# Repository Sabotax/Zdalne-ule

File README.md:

# Zdalne-ule
Projekt przejściowy oraz praca inżynierska oraz projekt kontynuowany prywatnie.
Polega na zbieraniu danych z uli pszczeli w celu ich zdalnego wykorzystania w optymalizacji pracy pszczelarza.  

Używane technologie: 
	- C++ od strony mikontrolerów,

 \
	- Javascript/PHP od strony serwera
 \
	- Kotlin od strony aplikacji mobilnej

Prezentacja  
https://prezi.com/view/HmCi9ISC9FMyPvuT7w0S/

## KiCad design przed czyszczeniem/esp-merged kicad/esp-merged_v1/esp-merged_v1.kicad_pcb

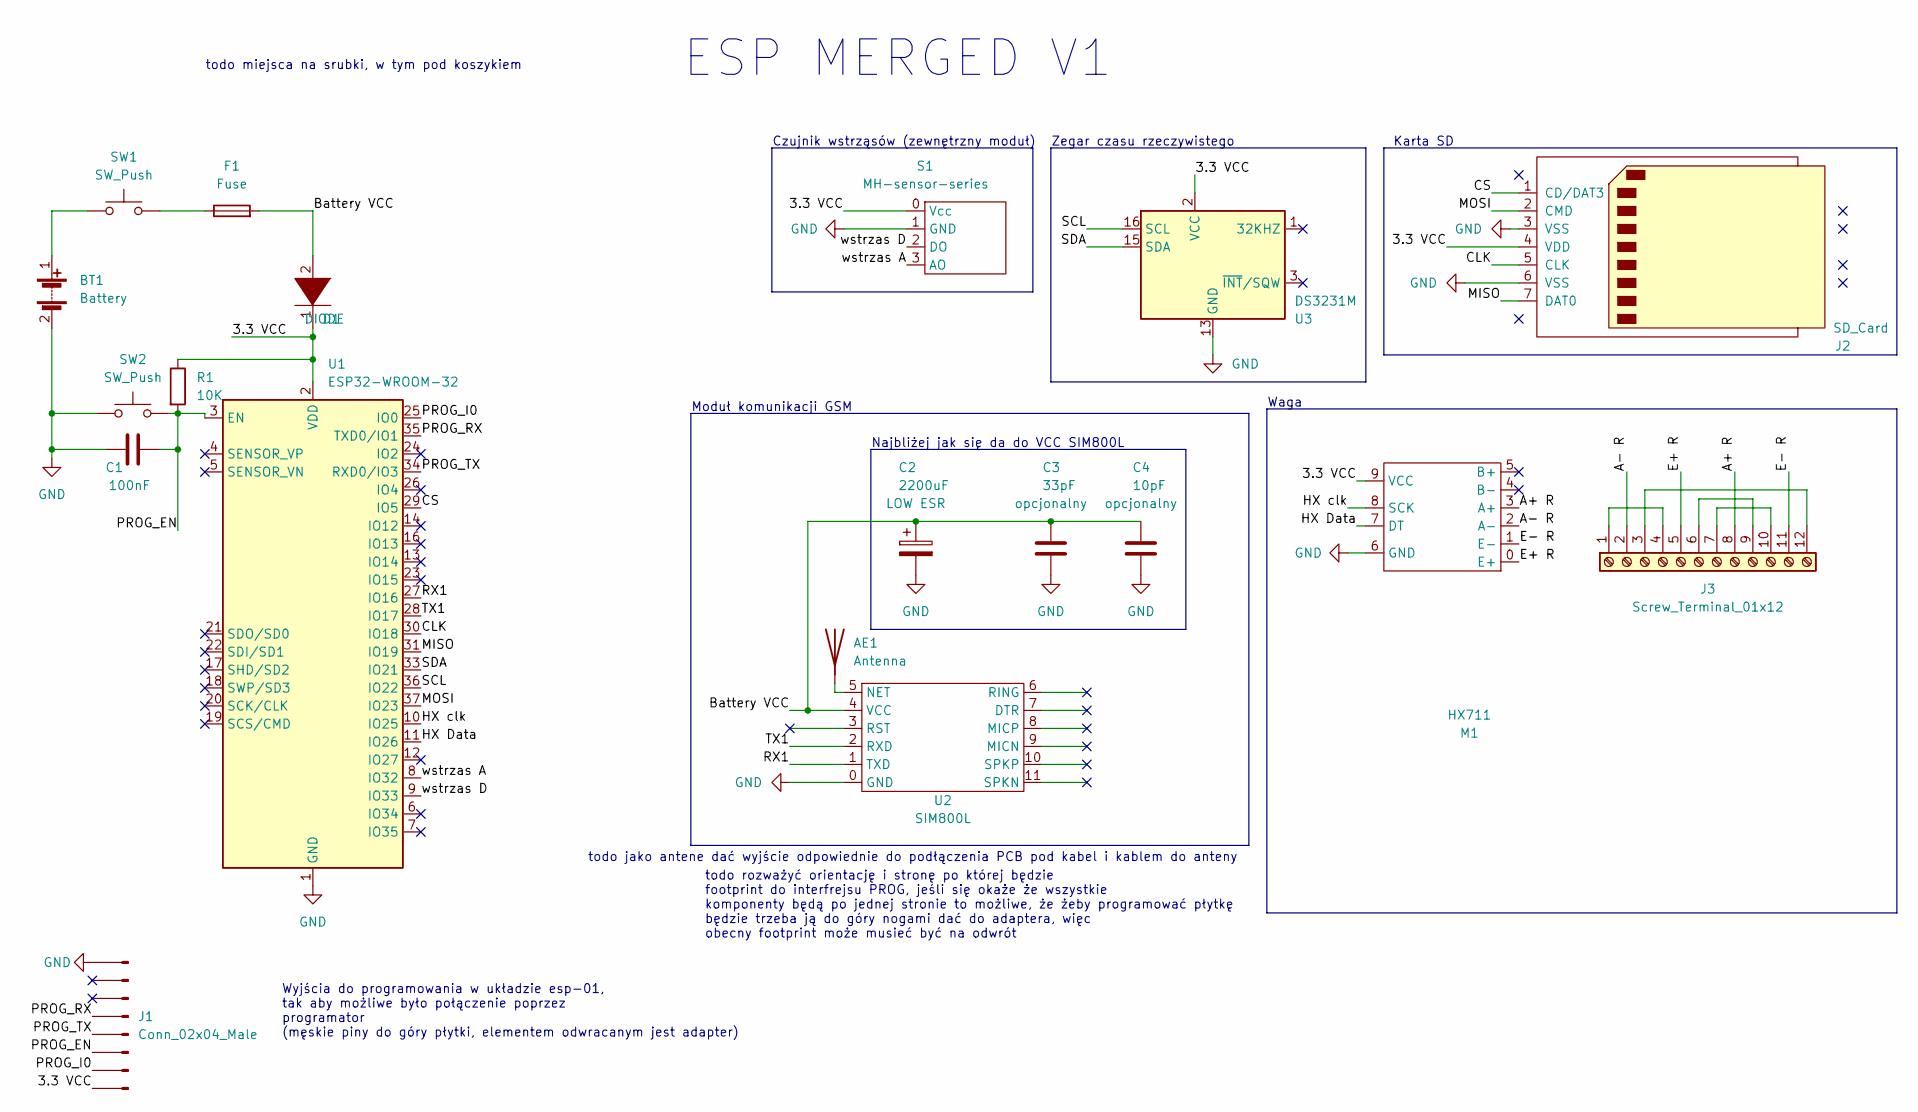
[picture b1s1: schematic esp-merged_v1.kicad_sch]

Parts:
AE1: Antenna; SMA_Amphenol_132291_Vertical
BT1: Battery; koszyk na baterie 1x1
C1: 100nF; CP_Radial_Tantal_D5.0mm_P2.50mm
C2: 2200uF; CP_Radial_D10.0mm_P5.00mm
C3: 33pF; CP_Radial_Tantal_D5.0mm_P2.50mm
C4: 10pF; CP_Radial_Tantal_D5.0mm_P2.50mm
D1: DIODE; D_A-405_P10.16mm_Horizontal
F1: Fuse; R_Axial_DIN0411_L9.9mm_D3.6mm_P15.24mm_Horizontal
J1: Conn_02x04_Male; prog pins ESP32 (aka esp01) v2 (odwrocone)
J2: SD_Card; karta sd
J3: Screw_Terminal_01x12; screw connector 12
M1: HX711; hx711
R1: 10K; R_Axial_DIN0207_L6.3mm_D2.5mm_P10.16mm_Horizontal
S1: MH-sensor-series
SW1: SW_Push; wlacznik
SW2: SW_Push; mały button
U1: ESP32-WROOM-32
U2: SIM800L; sim800l
U3: DS3231M; ds3231

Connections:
/3.3 VCC: D1.1 (A), J1.1, J2.4 (VDD), M1.9 (VCC), R1.1, S1.0 (Vcc), U1.2 (VDD), U3.2 (VCC)
/A+ R: J3.8, M1.3 (A+)
/A- R: J3.2, M1.2 (A-)
/Battery VCC: C2.1, C3.1, C4.1, D1.2 (K), F1.2, U2.4 (VCC)
/CLK: J2.5 (CLK), U1.30 (IO18)
/CS: J2.1 (CD/DAT3), U1.29 (IO5)
/E+ R: J3.5, M1.0 (E+)
/E- R: J3.11, M1.1 (E-)
/HX Data: M1.7 (DT), U1.11 (IO26)
/HX clk: M1.8 (SCK), U1.10 (IO25)
/MISO: J2.7 (DAT0), U1.31 (IO19)
/MOSI: J2.2 (CMD), U1.37 (IO23)
/PROG_EN: C1.2, J1.3, R1.2, SW2.2, U1.3 (EN)
/PROG_I0: J1.2, U1.25 (IO0)
/PROG_RX: J1.5, U1.35 (TXD0/IO1)
/PROG_TX: J1.4, U1.34 (RXD0/IO3)
/RX1: U1.27 (IO16), U2.1 (TXD)
/SCL: U1.36 (IO22), U3.16 (SCL)
/SDA: U1.33 (IO21), U3.15 (SDA)
/TX1: U1.28 (IO17), U2.2 (RXD)
/wstrzas A: S1.3 (AO), U1.8 (IO32)
/wstrzas D: S1.2 (DO), U1.9 (IO33)
GND: BT1.2 (-), C1.1, C2.2, C3.2, C4.2, J1.8, J2.3 (VSS), J2.6 (VSS), M1.6 (GND), S1.1 (GND), SW2.1, U1.1 (GND), U1.15 (GND), U1.38 (GND), U1.39 (GND), U2.0 (GND), U3.13 (GND)
unnamed: AE1.1 (A), U2.5 (NET)
unnamed: BT1.1 (+), SW1.1
unnamed: F1.1, SW1.2
unnamed: J3.1, J3.4
unnamed: J3.6, J3.9
unnamed: J3.7, J3.10
unnamed: J3.3, J3.12

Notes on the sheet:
ESP MERGED V1
Karta SD
todo rozważyć orientację i stronę po której będzie footprint do interfrejsu PROG, jeśli się okaże że wszystkie komponenty będą po jednej stronie to możliwe, że żeby programować płytkę będzie trzeba ją do góry nogami dać do adaptera, więc obecny footprint może musieć być na odwrót
Najbliżej jak się da do VCC SIM800L
Czujnik wstrząsów (zewnętrzny moduł)
Zegar czasu rzeczywistego
todo jako antene dać wyjście odpowiednie do podłączenia PCB pod kabel i kablem do anteny
Waga
Moduł komunikacji GSM
Wyjścia do programowania w układzie esp-01, tak aby możliwe było połączenie poprzez programator (męskie piny do góry płytki, elementem odwracanym jest adapter)
todo miejsca na srubki, w tym pod koszykiem

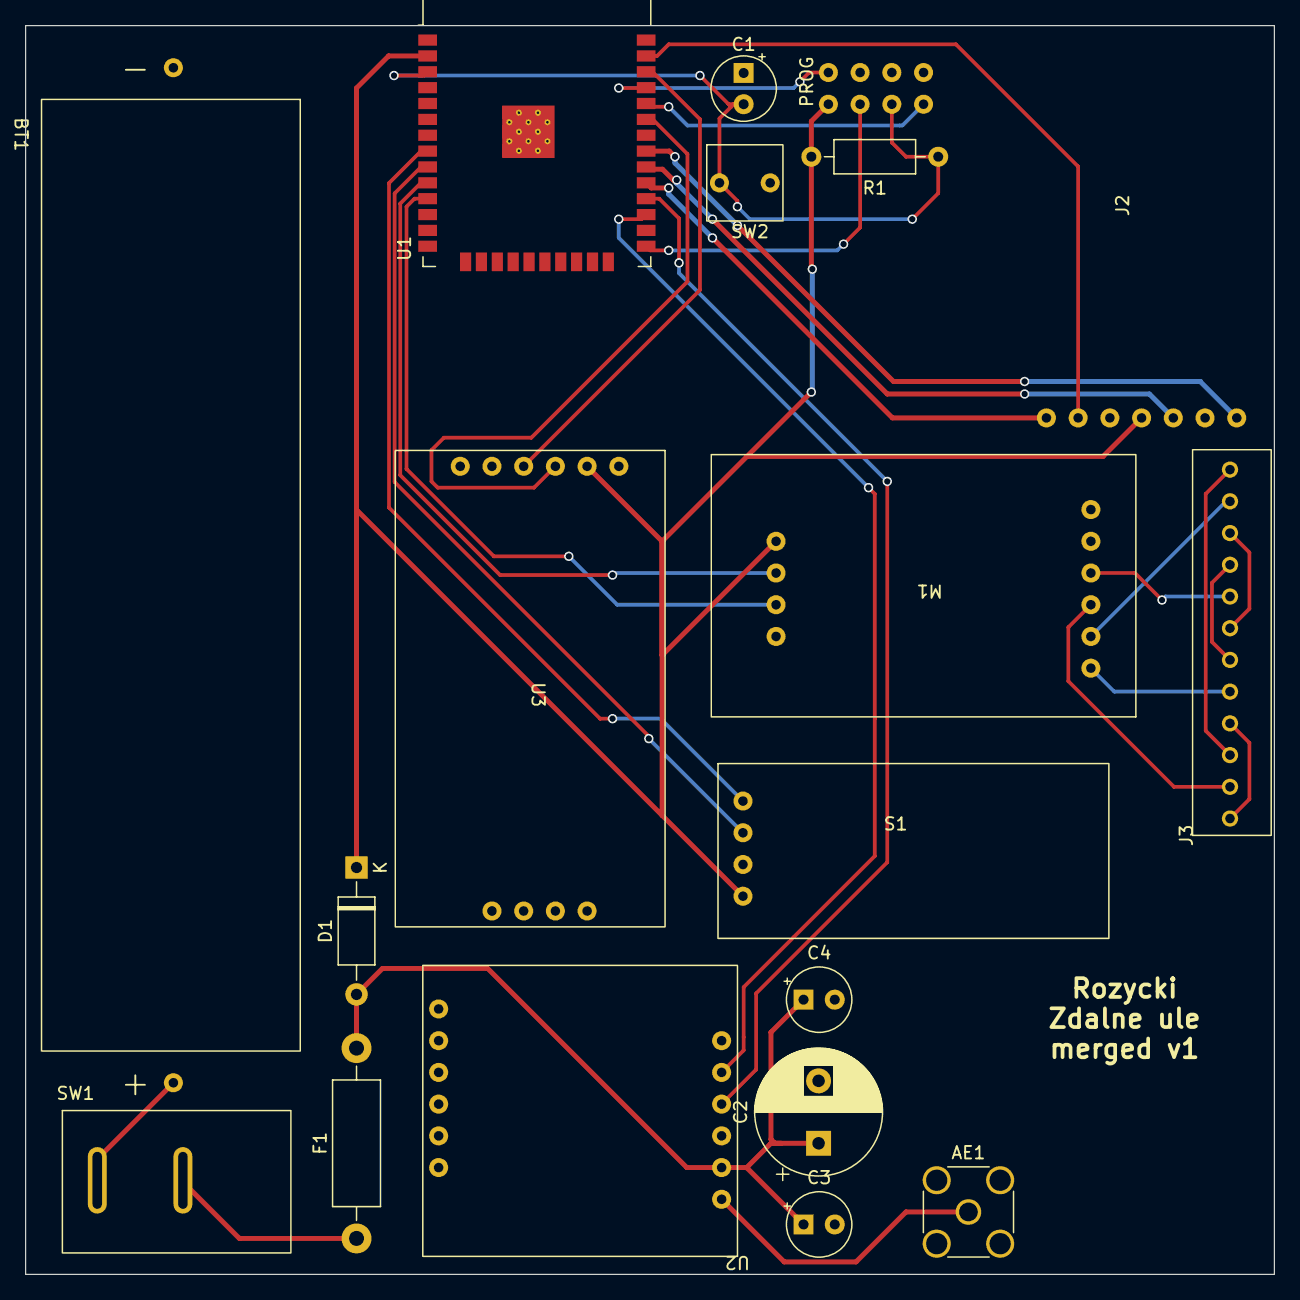
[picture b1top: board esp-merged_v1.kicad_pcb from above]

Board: 2 copper layers, 100.0 x 100.0 mm, 19 parts (0 on the bottom side), 30 nets.

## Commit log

2022-03-01 szkic v2
2022-03-01 linki
2022-03-02 testy na nodemcu oraz początek próby obługi zewnętrznego esp8266
    w celu takim, że można te kompononty wysłać do domu i zrobić szybki prototyp do wyświetlania informacji z wagi,temperatury itp przed rozpoczęciem sezonu zbiorów, dzięki temu można zacząć zbierać (skr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
2022-03-03 kod nieprzetestowany do uno+esp8266 zewnetrzne+accesspoint+webserver
2022-03-04 pierwsze pomyślne próby użycia esp-01 8266 jako modułu wifi i AP
2022-03-05 próby sflashowania esp-01 (nieudane)
2022-03-07 szamotanie się z AT, destabilizacja firmware, odkrycie stulecia że można użyć arduino IDE bezpośrednio na esp-01
2022-03-13 spis elementów
2022-03-15 sonda_temperatury_działa
2022-03-16 czujnik wibracji done
2022-03-23 telnet server dzialajacy
2022-03-23 plan
2022-03-24 waga polutowane, kod kalibracji
2022-04-06 projekt v1 - offline pomiary - poczatek (Sensor.Temperatura)
2022-04-07 Waga,Save
2022-04-07 Timer&Sleep synchornizowane
    kompiluje sie, dzialanie niesprawdzane
2022-04-08 main
2022-04-09 prawie dziala
    po obudzeniu wyglada jakby od nowa uruchamialo setup() ? - niezidentyfikowane działanie, czy budzi się po lini po której zasnęło, czy od loop() czy od setup() czy może w ogóle przez problem z pamicią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
2022-04-10 timer1
2022-04-10 uproszczony projekt od nowa
2022-04-10 działający offline pomiar ze spaniem bez interruptu
2022-04-17 flush fix offline zbieranie
2022-04-25 bezowocne próby budzenia esp8266 poprzez alarm z ds3231
2022-04-26 wszystko dzała oprócz wagi
2022-04-26 działa, ale bez sleep
2022-04-26 działa, czas lutować
2022-04-26 job done v3 zbieranie offline
    TODO ostatecznie rozwiązać kwestię akumulatora, bo te które mam są risky dla 3v3 (dają do 3.8, a wg dokumentacji 3.6 [wg hakierów nawet 4 szło ale się grzeje no i ryzykowne]), ale też są za słabe dla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
2022-05-07 online proba1 v1
2022-05-08 zasypanie,mierzenie,wysylanie slave + odbieranie tego przez master
2022-06-11 master&slave comms v2 [untested]
2022-06-12 master & slave presentation ready
2022-06-15 esp32 read from site
    esp32 correctly connects through wifi to my site at pp and gets whole information (example_wificlient.ino)
2022-06-22 start konwersji esp-master na esp32 + pierwsze kroki komunikacji calościowej
2022-06-22 uporządkowana struktura + podział na 2 programy do esp-master
    poniewaz latwiej na interfejsie wifi sprawdzac polaczenie z chmura, ale nie moge go jednosczesnie uzywac zeby AP robic, gsm bardzo podobnie dziala pozniej wiec podmiana powinna byc latwa
2022-06-22 cleaned masterv3zewn
2022-06-25 reorganizacja + wysylanie do php jsona
2022-06-25 array of objects to json to php server i z powrotem
2022-06-26 "definitywna" jsonowa struktura i dziala wysylanie i intepretowanie
2022-06-26 php insert unique
    query przetestowane, dzialanie php nie, unique poniewaz te same krotki moga trafic do DB z roznych zrodel (esp-master ->gsm->DB) ale też (esp-master->android -> gsm->DB) itp
2022-06-26 /index( show) & /insert (insert)
2022-06-26 front start
2022-06-26 plan fazy 2
    w index_program.php
2022-06-28 front
    merge folderów php i front oraz praca na nich w htdocs
2022-06-28 web selector + ajax
2022-06-28 wyobrebniłem plan i zaktualizowałem
2022-07-02 chart i opcje do niego
2022-07-02 sql query for charts
    also charts almost implemented
2022-07-03 asynchrous await na odpowiedz ajaxa zeby rysowac
2022-07-03 front poprawiony, wykresy autorysowane na podstawie danych z tabeli
2022-07-03 przegranie na live server i fixy z tym związane
    inne dane do logowania, dodatkowo header jakiś tam do corb (już niepotrzebny pewnie) i inne naprawy
2022-07-20 udało się skomunikować pomyślnie z SIM800L
2022-08-07 AT talk 1
    w Poznaniu sygnal bez anteny ma 21/32 mocy -> czyli dobór anteny można na później zostawić
2022-09-03 rozmowy kolejne
2022-09-25 próby rozmowy z SIM900A oraz rozpoczęcie BLE client-serwer (działające przesyłanie stringa)
2022-09-25 przebiegi z oscyloskopu
2022-09-25 reakcja na write i plan
2022-09-26 działające
2022-10-02 nowa wersja gotowa do testow i odrobine odpowiedzi na serwerze
2022-10-05 prawidłowa komunikacja z serwerem potwierdzona :)
2022-10-05 v0.6 z kartą sd i docelowym zbieraniem z telefonu start i założenia w SD.h
2022-10-05 plan na kartę i przesyłanie danych
2022-10-07 add SD, not tested
2022-10-18 cos tam
2022-10-19 sms wysłany i pomyślnie odebrany
2022-10-19 kondensatory jakie wziac notka
2022-10-22 kopia v06 nie ruszona
2022-10-22 szkic do lutowania , work in progress
2022-10-25 backup
2022-11-02 v1 działa, todo przeniesc na bilbioteki
2022-11-02 tiny gsm dziala
2022-11-04 master teoretycznie z działającym tiny gsm, nietestowane
2022-11-04 poczatki insert into db
2022-11-04 add token to espmaster
2022-11-05 teoretycznie dostosowane insertowanie do bazy
2022-11-05 sprawdzone poprawione, wkladanie danych
2022-11-12 kalibraxja
2023-01-24 układy elektryczne i prezentacja
2023-01-25 zmiany mastera?? teraz działa ale wcześniej kilka miesięcy temu też działało?
2023-03-09 schemat wzm pomiarowego
2023-03-09 kalibracja wagi krzywą 0-15kg
2023-04-04 kalibracja czujników tenso
2023-04-19 esp merged kicad
2023-04-26 postępy projektowania PCB
2023-04-28 postepy kicad, footprinty
2023-04-28 kicad footprint sim800l
2023-05-01 pcb skonczone?
2023-05-01 esp merged pcb v2 (dostosowane pod obudowe)
2023-06-25 touch wake up working
2023-06-26 ble synch in progress, esp side
2023-06-26 remove client ble
2023-06-28 esp side finished?
2023-06-28 working pomiar and probably synch
2023-06-28 change date filename
2023-06-30 przykładowy kod do uzupełnienia bit array
2023-07-01 działające synchronizowanie dnia
2023-07-19 set scale and offset and store in rtc
2023-07-22 b
    b
2023-07-27 skalibrowane
2023-07-27 hide connection data
2023-07-27 dostosowanie serwera do nowych realiów
2023-07-27 move auth
2023-07-30 gsm working in merged.ino, interface for BLE-read-battery
2023-08-23 w koncu działające wysyłanie POST na SIM800L
2023-08-24 v3, no tinyGSM, only AT
2023-09-16 #ifdef
2023-09-21 reorder most of files, yoink "Aplikacja 6 sem" to "kod aplikacja"
2023-09-22 readme md update
2023-11-07 wiecej funkcji do rozmowy z telefonem
2023-11-08 2 wersja, fix na pierwsza
2023-11-08 wake up btn and led in code
2023-11-09 wake up by btn and led
2023-11-11 fix to rtc setting time each time to compilatiion time
2023-11-11 adjust synch to send weight bigger than 255
2023-11-12 początki fixów do schematu pcb v2
2023-11-12 add battery level to chart and saving in table
2024-02-17 a
    a
2024-02-18 c
    c
2024-02-21 inicjacja setTime
2024-02-25 ble fix
2024-02-25 naprawa czyszczenia wykresow (starych danych)
2024-02-25 time synch (not tested)
    cant connect to BLE, works once per 10 tries (after resetting)
2024-02-25 ustawienie czasu działa,
    ble też działa jednak, tylko nie może być zakłóceń między serwerem a klientem (np komputer, laptop, monitor klawiatura jednocześnie + 2m)
2024-02-28 maly progress pcb
2024-04-03 app front adjustments
2024-05-05 ledy zmiana
2024-05-06 początki v4 (no sleep, non blocking loop with gsm itp)
    non blocking gsm init (oby)
2024-05-07 dalsze prace, non blocking post gsm
2024-05-07 kolejne funkcje
2024-05-12 debugowanie async
2024-05-13 działający async init gsm
2024-05-13 timer dzialajacy wraz z async initem
    przeanalizować ostatni .txt, poprawic postGSM tak jak poprawiono initGSM
2024-05-15 finished working post and comms
2024-05-15 wyczajone LDO i konwertery logiki
2024-05-15 na zywym obiekcie, wszystko dziala oprocz zapisu/odczytu SD
